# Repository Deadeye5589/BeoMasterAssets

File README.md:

This repo consists of files needed for the BeoMaster Amp project.
It includes
Schematic and layout for main DSP PCB
Schematic and layout for 230 V power distribution PCB
Fusion360 and SVG files to lasercut front display construction
PDS files for left and right display graphics
Square Line Studio projects for left and right display content

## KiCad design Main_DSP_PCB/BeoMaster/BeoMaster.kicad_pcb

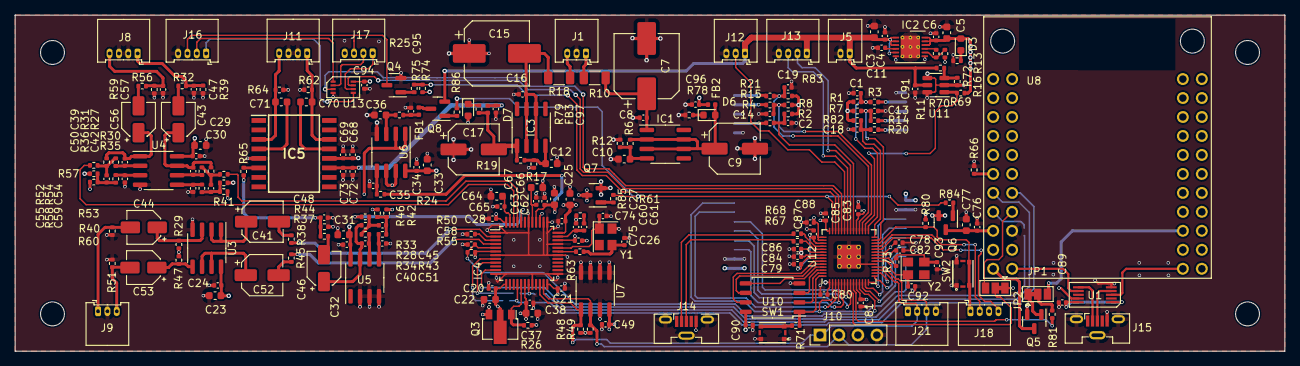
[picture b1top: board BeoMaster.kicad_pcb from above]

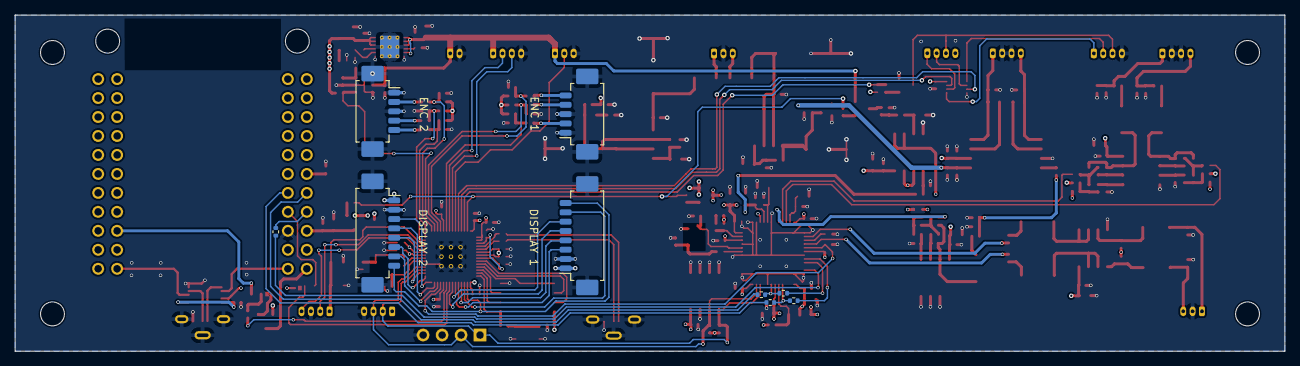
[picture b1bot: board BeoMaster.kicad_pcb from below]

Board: 4 copper layers, 170.0 x 45.0 mm, 238 parts (9 on the bottom side), 160 nets.

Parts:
C1, C2, C4, C6, C13, C14, C18, C19, C20, C21, C24, C26, C27, C28, C30, C32, C34, C35, C38, C49, C58, C63, C65, C67, C69, C73, C76, C89: 100nF; C_0402_1005Metric
C3, C5, C10, C12, C22, C23, C25, C29, C31, C33, C37, C62, C64, C66, C70, C71, C77: 10µF; C_0603_1608Metric
C7, C15: 220µF; CP_Elec_8x10.5
C8, C16: 220nF; C_0402_1005Metric
C9, C17: 100µF; CP_Elec_6.3x5.8
C11, C95, C96, C97: 10nF; C_0402_1005Metric
C36: 2.2µF; C_0603_1608Metric
C39, C40, C50, C51, C54, C59: 150pF; C_0402_1005Metric
C41, C52: 47µF; CP_Elec_5x5.8
C42, C45, C55: 1nF; C_0402_1005Metric
C43, C46, C56: 10µF; CP_Elec_4x5.4
C44, C53: 2.2µF; CP_Elec_4x5.4
C47, C48, C57, C60: 3n3; C_0402_1005Metric
C61: 56nF; C_0402_1005Metric
C68, C72: 1µF; C_0402_1005Metric
C74, C75: 18pF; C_0402_1005Metric
C78, C79, C80, C81, C82, C83, C84, C85, C86, C90, C91, C94: 100n; C_0402_1005Metric
C87, C88: 1u; C_0402_1005Metric
C92, C93: 18p; C_0402_1005Metric
D3, D6, D7: LED; LED_0603_1608Metric
FB1, FB2, FB3: 300@1MHz; L_0402_1005Metric
H1, H2, H3, H4: MountingHole; MountingHole_3.2mm_M3_ISO14580
IC1: LM317L_SO8; SOIC-8_3.9x4.9mm_P1.27mm
IC2: LP38798; WSON-12-1EP_4x4mm_P0.5mm_EP2.6x3mm_ThermalVias
IC3: LM337L_SO8; SOIC-8_3.9x4.9mm_P1.27mm
IC4: ADAU1701JSTZ; LQFP-48_7x7mm_P0.5mm
IC5: DRV134UA; SOIC127P1030X265-16N
J1: 24V_In; Molex_PicoBlade_53048-0310_1x03_P1.25mm_Horizontal
J2: Encoder_Links; Molex_PicoBlade_53261-0571_1x05-1MP_P1.25mm_Horizontal
J3: Encoder_Rechts; Molex_PicoBlade_53261-0571_1x05-1MP_P1.25mm_Horizontal
J4: Display_Links; Molex_PicoBlade_53261-0871_1x08-1MP_P1.25mm_Horizontal
J5: 5V_In; Molex_PicoBlade_53048-0210_1x02_P1.25mm_Horizontal
J6: Display_Rechts; Molex_PicoBlade_53261-0871_1x08-1MP_P1.25mm_Horizontal
J8: Audio_Out; Molex_PicoBlade_53048-0410_1x04_P1.25mm_Horizontal
J9: Aux_In; Molex_PicoBlade_53048-0310_1x03_P1.25mm_Horizontal
J10: DSP_Debugger; PinHeader_1x04_P2.54mm_Vertical
J11: Diff_Out; Molex_PicoBlade_53048-0410_1x04_P1.25mm_Horizontal
J12: WS2812; Molex_PicoBlade_53048-0310_1x03_P1.25mm_Horizontal
J13: 220V_Relais; Molex_PicoBlade_53048-0410_1x04_P1.25mm_Horizontal
J14: RPI_USB; USB_Micro-B_Molex-105133-0031
J15: USB_Audio; USB_Micro-B_Molex-105133-0031
J16: AMP_CTRL1; Molex_PicoBlade_53048-0410_1x04_P1.25mm_Horizontal
J17: AMP_CTRL2; Molex_PicoBlade_53048-0410_1x04_P1.25mm_Horizontal
J18: RP_SWD; Molex_PicoBlade_53048-0410_1x04_P1.25mm_Horizontal
J21: I2C_TempSensor; Molex_PicoBlade_53048-0410_1x04_P1.25mm_Horizontal
JP1, JP2: SolderJumper_3_Bridged12; SolderJumper-3_P1.3mm_Bridged12_Pad1.0x1.5mm
Q3: ZXTP25040DZTA; SOT-89-3
Q4: BC816H; SOT-23
Q5, Q6, Q7, Q8: IRLML2244; SOT-23
R1, R2, R3, R4, R7, R8, R14, R15, R20, R21, R26, R31, R34, R36, R43, R54, R58, R65, R71, R73, R75, R82, R83: 1k; R_0402_1005Metric
R6, R19, R62, R64: 220; R_0402_1005Metric
R10, R18: 100; R_1206_3216Metric
R11: 23k7; R_0402_1005Metric
R12, R17: 2k; R_0402_1005Metric
R13: 180; R_0402_1005Metric
R16: 13k3; R_0402_1005Metric
R24, R30, R33, R35, R42, R53, R55, R57, R66, R69, R70, R74, R80: 10k; R_0402_1005Metric
R25, R29, R47: 100k; R_0402_1005Metric
R27, R28, R41, R46, R52, R60: 22k; R_0402_1005Metric
R32, R37, R56: 680; R_0402_1005Metric
R38, R45, R72: 18k; R_0402_1005Metric
R39, R40, R44, R51, R59: 47k; R_0402_1005Metric
R48, R49: 2k2; R_0402_1005Metric
R50: 18k2; R_0402_1005Metric
R61: 475; R_0402_1005Metric
R63, R81, R84, R85, R86: 100; R_0402_1005Metric
R67, R68: 27; R_0402_1005Metric
R78, R79: 820; R_0402_1005Metric
R87, R88, R89, R90, R91: 22; R_0402_1005Metric
SW1: BOOT; SKSG
SW2: RESET; SKSG
U1: TS3USB30E; TEXAS_VSSOP_10_P0.5
U3, U4, U5, U6: LME49720; SOIC-8_3.9x4.9mm_P1.27mm
U7: 24LC256 (SN); SOIC-8_3.9x4.9mm_P1.27mm
U8: CSRA64215; CSR64215
U10: W25Q128JVS; SOIC-8_5.23x5.23mm_P1.27mm
U11: TPS3711; SOT-23-6
U12: RP2040; RP2040-QFN-56
U13: NC7WZ38; US8 -OnSemi
Y1: 12.288MHz; Crystal_SMD_3225-4Pin_3.2x2.5mm
Y2: 12 MHz; Crystal_SMD_3225-4Pin_3.2x2.5mm

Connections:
+1V1: C78.1, C79.1, C87.1, U12.23 (DVDD), U12.45 (VREG_VOUT), U12.50 (DVDD)
+1V5: R35.1, R42.1, R57.1, U6.6 (-), U6.7
+1V8: C20.1, C21.1, C22.1, IC4.13 (DVDD), IC4.24 (DVDD), Q3.2 (C)
+3.3VP: C25.1, C26.1, C27.1, C28.1, C37.1, C38.1, C49.1, C60.2, IC4.6 (SELFBOOT), IC4.18 (IOVDD), IC4.34 (PVDD), IC4.36 (AVDD), IC4.39 (PLL_MOD1), IC4.48 (AVDD), Q3.3 (E), Q7.3 (D), R26.1, R48.1, R49.1, R55.1, R61.1, U7.8 (VCC)
+3V3: C5.1, C6.1, C80.1, C81.1, C82.1, C83.1, C84.1, C85.1, C86.1, C88.1, C89.1, C90.1, C94.1, D3.2 (A), IC2.10 (OUT_(FB)), IC2.11 (OUT), IC2.12 (OUT), J4.1, J6.1, J21.1, Q5.2 (S), Q6.2 (S), Q7.2 (S), R1.2, R2.2, R7.2, R8.2, R69.1, R74.1, R80.1, R82.2, R83.2, U1.1 (S), U1.10 (Vcc), U10.8 (VCC), U12.1 (IOVDD), U12.10 (IOVDD), U12.22 (IOVDD), U12.33 (IOVDD), U12.42 (IOVDD), U12.43 (ADC_AVDD), U12.44 (VREG_IN), U12.48 (USB_VDD), U12.49 (IOVDD), U13.8 (Vcc)
+5V: C3.1, C4.1, C91.1, IC2.1 (IN), IC2.2 (IN), IC2.3 (IN_(CP)), IC2.5 (EN), J5.1, J12.1, J13.1, Q8.2 (S), R70.1, U11.5 (VDD)
+5VA: R29.1, R41.2, R46.2, R47.1, R60.2, U6.1, U6.2 (-)
+12V: C23.1, C24.1, C29.1, C30.1, C31.1, C32.1, C33.1, C34.1, C68.1, C69.1, C96.1, FB2.2, IC5.12 (V+), U3.8 (V+), U4.8 (V+), U5.8 (V+), U6.8 (V+)
-12V: C72.2, C73.2, C97.2, FB3.2, IC5.11 (V-)
/AMP_MUTE: R74.2, R75.2, U12.40 (GPIO28_ADC2)
/QSPI_SCLK: U10.6 (CLK), U12.52 (QSPI_SCLK)
/QSPI_SD0: U10.5 (DI(IO0)), U12.53 (QSPI_SD0)
/QSPI_SD1: U10.2 (DO(IO1)), U12.55 (QSPI_SD1)
/QSPI_SD2: U10.3 (IO2), U12.54 (QSPI_SD2)
/QSPI_SD3: U10.7 (IO3), U12.51 (QSPI_SD3)
/QSPI_SS: R71.1, U10.1 (~CS), U12.56 (QSPI_SS)
/RUN: J18.1, R80.2, SW2.2, U12.26 (RUN)
/SSR1: J13.2, U12.35 (GPIO23)
/SSR2: J13.3, U12.36 (GPIO24)
/SWCLK: J18.4, U12.24 (SWCLK)
/SWD: J18.2, U12.25 (SWD)
/USB_D+: J14.3 (D+), R67.1
/USB_D-: J14.2 (D-), R68.1
/USB_N: U1.7 (D2-), U8.2 (USBN)
/USB_P: U1.3 (D2+), U8.23 (USBP)
/V_SENS: R69.2, U11.1 (OUT), U12.30 (GPIO19)
/Vin+: J1.1, R10.1
/Vin-: J1.3, R18.1
/XIN: C92.1, U12.20 (XIN), Y2.1
/XOUT: R73.1, U12.21 (XOUT)
/~USB_BOOT: R71.2, SW1.2
AMP_MUTE_CONN: J16.3, J17.3, Q4.3 (C)
AMP_OC: U12.39 (GPIO27_ADC1), U13.7 (Y1)
AMP_TEMP: U12.38 (GPIO26_ADC0), U13.3 (Y2)
Analog_In0: IC4.45 (VOUT1), R30.1
Analog_In1: IC4.46 (VOUT0), R53.1
Analog_Out0: C47.1, J8.1, R32.2, R39.1
Analog_Out1: C57.1, J8.4, R56.2, R59.1
BCLK: R90.2, U8.9 (CLK)
BT_MFB: R81.1, U12.9 (GPIO7)
BT_RST: JP2.2 (C), U12.8 (GPIO6)
CM: C62.1, C63.1, IC4.40 (CM), R24.2
DISP_BL: J4.8, J6.8, U12.2 (GPIO0)
DISP_CLK1: J4.4, U12.13 (GPIO10)
DISP_CLK2: J6.4, U12.4 (GPIO2)
DISP_CS1: J4.5, U12.16 (GPIO13)
DISP_CS2: J6.5, U12.7 (GPIO5)
DISP_DC1: J4.6, U12.15 (GPIO12)
DISP_DC2: J6.6, U12.6 (GPIO4)
DISP_DIN1: J4.3, U12.14 (GPIO11)
DISP_DIN2: J6.3, U12.5 (GPIO3)
DISP_RST1: J4.7, U12.12 (GPIO9)
DISP_RST2: J6.7, U12.3 (GPIO1)
DSP_RESET: C58.1, IC4.5 (~RESET), J10.3, R55.2, U12.11 (GPIO8)
Diff_In0: IC4.44 (VOUT2), R33.1
Diff_Out0: C48.1, R37.2, R44.1, R65.2
Diff_Out0+: C70.1, IC5.14 (+Vo), J11.1, R62.1
Diff_Out0-: C71.2, IC5.3 (-Vo), J11.4, R64.2
ENC1_A: C13.1, R7.1, R14.2, U12.27 (GPIO16)
ENC1_B: C18.1, R20.2, R82.1, U12.28 (GPIO17)
ENC1_SW: C1.1, R1.1, R3.2, U12.29 (GPIO18)
ENC2_A: C14.1, R8.1, R15.2, U12.31 (GPIO20)
ENC2_B: C19.1, R21.2, R83.1, U12.32 (GPIO21)
ENC2_SW: C2.1, R2.1, R4.2, U12.34 (GPIO22)
GND: C1.2, C2.2, C3.2, C4.2, C5.2, C6.2, C7.2, C8.2, C9.2, C10.2, C11.2, C12.2, C13.2, C14.2, C15.1, C16.2, C17.1, C18.2, C19.2, C20.2, C21.2, C22.2, C23.2, C24.2, C25.2, C26.2, C27.2, C28.2, C29.2, C30.2, C31.2, C32.2, C33.2, C34.2, C35.2, C36.2, C37.2, C38.2, C47.2, C48.2, C49.2, C50.2, C51.2, C57.2, C58.2, C59.2, C62.2, C63.2, C64.2, C65.2, C66.2, C67.2, C68.2, C69.2, C72.1, C73.1, C74.2, C75.2, C76.2, C77.2, C78.2, C79.2, C80.2, C81.2, C82.2, C83.2, C84.2, C85.2, C86.2, C87.2, C88.2, C89.2, C90.2, C91.2, C92.2, C93.2, C94.2, C95.2, C96.2, C97.1, D7.2 (A), IC2.6 (GND_(CP)), IC2.7 (GND), IC2.13 (EP), IC4.1 (AGND), IC4.7 (ADDR0), IC4.12 (DGND), IC4.20 (ADDR1), IC4.25 (DGND), IC4.30 (RSVD), IC4.33 (PGND), IC4.37 (AGND), IC4.38 (PLL_MOD0), IC4.42 (AGND), IC5.5 (GND), J1.2, J2.1, J2.3, J2.MP, J3.1, J3.3, J3.MP, J4.2, J4.MP, J5.2, J6.2, J6.MP, J8.2, J8.3, J9.2, J10.4, J11.2, J11.3, J12.3, J13.4, J14.5 (GND), J14.6 (Shield), J15.5 (GND), J15.6 (Shield), J16.4, J18.3, J21.4, Q4.2 (E), R12.2, R13.2, R16.2, R17.1, R39.2, R40.2, R44.2, R50.2, R51.2, R59.2, R62.2, R64.1, R66.2, R72.2, R78.2, SW1.1, SW2.1, U1.5 (GND), U3.4 (V-), U4.4 (V-), U5.2 (-), U5.3 (+), U5.4 (V-), U6.4 (V-), U7.1 (A0), U7.2 (A1), U7.3 (A2), U7.4 (GND), U7.7 (WP), U8.6 (GND), U10.4 (GND), U11.2 (GND), U11.4 (GND), U11.6 (GND), U12.19 (TESTEN), U12.57 (GND), U13.4 (GND), Y1.4
LRCLK: R91.2, U8.10 (CSB)
unnamed: C15.2, C16.1, IC3.2 (VI), IC3.3 (VI), IC3.6 (VI), IC3.7 (VI), R18.2
unnamed: C39.1, C43.1, R27.1, U4.7
unnamed: C40.1, C46.1, R28.1, U5.7
unnamed: C41.2, R38.2
unnamed: C42.1, R27.2, R30.2, R31.1
unnamed: C42.2, R35.2, R36.2, R41.1
unnamed: C43.2, R32.1
unnamed: C45.1, R28.2, R33.2, R34.1
unnamed: C45.2, R42.2, R43.2, R46.1
unnamed: C46.2, R37.1
unnamed: C52.2, R45.2
unnamed: C54.1, C56.1, R52.1, U4.1
unnamed: C55.1, R52.2, R53.2, R54.1
unnamed: C55.2, R57.2, R58.2, R60.1
unnamed: C56.2, R56.1
unnamed: C61.2, R61.2
unnamed: C75.1, R63.2, Y1.3
unnamed: C93.1, R73.2, Y2.3
unnamed: C95.1, FB1.2, R25.2
unnamed: D3.1 (K), R13.1
unnamed: C9.1, D6.2 (A), FB2.1, IC1.2 (VO), IC1.3 (VO), IC1.6 (VO), IC1.7 (VO), R6.1
unnamed: D6.1 (K), R78.1
unnamed: D7.1 (K), R79.1
unnamed: C10.1, IC1.4 (ADJ), R6.2, R12.1
unnamed: C7.1, C8.1, IC1.1 (VI), R10.2
unnamed: C11.1, IC2.4 (CP)
unnamed: IC2.8 (FB), R11.2, R16.1
unnamed: IC2.9 (SET), R11.1
unnamed: C12.1, IC3.4 (ADJ), R17.2, R19.1
unnamed: C17.2, FB3.1, IC3.1 (VO), R19.2, R79.2
unnamed: IC4.2 (ADC0), R38.1
unnamed: IC4.4 (ADC1), R45.1
unnamed: IC4.3 (ADC_RES), R50.1
unnamed: C64.1, C65.1, IC4.47 (FILTA)
unnamed: C66.1, C67.1, IC4.41 (FILTD)
unnamed: C74.1, IC4.32 (MCLKI), Y1.1
unnamed: IC4.8 (MP4), R89.1
unnamed: IC4.9 (MP5), R88.1
unnamed: IC4.16 (MP10), R89.2, R91.1
unnamed: IC4.19 (MP11), R88.2, R90.1
unnamed: IC4.31 (OSCO), R63.1
unnamed: C60.1, C61.1, IC4.35 (PLL_LF)
unnamed: IC4.17 (VDRIVE), Q3.1 (B), R26.2
unnamed: C70.2, IC5.13 (+Sense)
unnamed: C71.1, IC5.4 (-Sense)
unnamed: IC5.6 (Vin), R65.1
unnamed: J2.2, R3.1
unnamed: J2.4, R14.1
unnamed: J2.5, R20.1
unnamed: J3.2, R4.1
unnamed: J3.4, R15.1
unnamed: J3.5, R21.1
unnamed: C44.2, J9.1, R40.1
unnamed: C53.2, J9.3, R51.1
unnamed: J15.3 (D+), U1.4 (D+)
unnamed: J15.2 (D-), U1.6 (D-)
unnamed: J16.1, U13.5 (A2)
unnamed: J16.2, U13.1 (A1)
unnamed: J17.1, U13.6 (B2)
unnamed: J17.2, U13.2 (B1)
unnamed: JP1.1 (A), Q5.1 (G)
unnamed: JP1.3 (B), U8.27 (MFB)
unnamed: JP1.2 (C), R81.2
unnamed: JP2.1 (A), U1.9 (~OE)
unnamed: JP2.3 (B), U8.8 (RST)
unnamed: Q4.1 (B), R75.1
unnamed: Q5.3 (D), U8.1 (VCHG)
unnamed: C76.1, C77.1, Q6.3 (D), U8.5 (VBAT)
unnamed: Q6.1 (G), R84.2
unnamed: Q7.1 (G), R85.2
unnamed: FB1.1, Q8.3 (D)
unnamed: Q8.1 (G), R86.2
unnamed: C44.1, R29.2, U3.3 (+)
unnamed: C41.1, U3.1, U3.2 (-)
unnamed: C53.1, R47.2, U3.5 (+)
unnamed: C52.1, U3.6 (-), U3.7
unnamed: C59.1, R58.1, U4.3 (+)
unnamed: C54.2, R54.2, U4.2 (-)
unnamed: C50.1, R36.1, U4.5 (+)
unnamed: C39.2, R31.2, U4.6 (-)
unnamed: C51.1, R43.1, U5.5 (+)
unnamed: C40.2, R34.2, U5.6 (-)
unnamed: C36.1, R25.1, U6.3 (+)
unnamed: C35.1, R24.1, U6.5 (+)
unnamed: R87.1, U8.7 (MISO)
unnamed: R66.1, U8.11 (SPIPCM)
unnamed: R70.2, R72.1, U11.3 (SENSE)
unnamed: R68.2, U12.46 (USB_DM)
unnamed: R67.2, U12.47 (USB_DP)
PWR_EN: R84.1, R85.1, R86.1, U12.41 (GPIO29_ADC3)
SCL: IC4.23 (SCL), J10.2, J21.3, R49.2, U7.6 (SCL), U12.18 (GPIO15)
SDA: IC4.22 (SDA), J10.1, J21.2, R48.2, U7.5 (SDA), U12.17 (GPIO14)
SDATA: IC4.11 (MP0), R87.2
WS2812: J12.2, U12.37 (GPIO25)

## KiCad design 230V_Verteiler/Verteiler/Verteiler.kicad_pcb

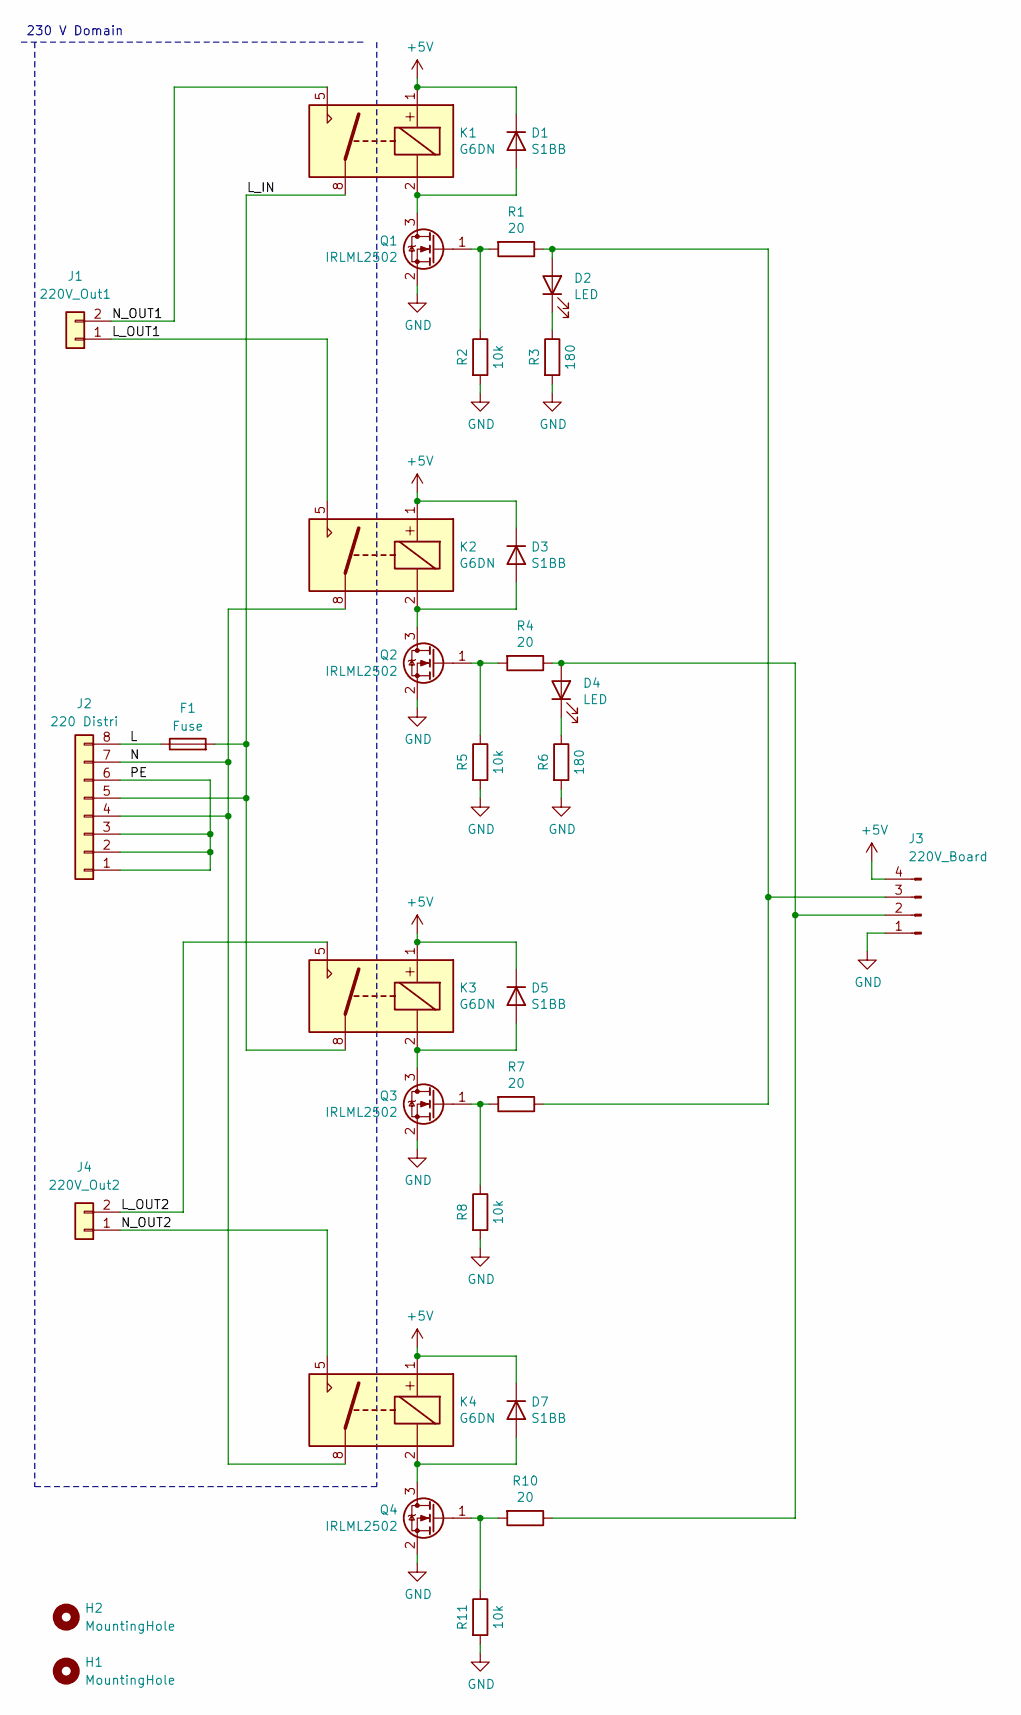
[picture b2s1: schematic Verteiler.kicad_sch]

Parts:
D1, D3, D5, D7: S1BB; D_SMB
D2, D4: LED; LED_0603_1608Metric
F1: Fuse; Fuseholder_Clip-5x20mm_Littelfuse_111_Lateral_P18.80x5.00mm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
H1, H2: MountingHole; MountingHole_3.2mm_M3
J1: 220V_Out1; PhoenixContact_MSTBA_2,5_2-G-5,08_1x02_P5.08mm_Horizontal
J2: 220 Distri; PhoenixContact_MSTBA_2,5_8-G-5,08_1x08_P5.08mm_Horizontal
J3: 220V_Board; Molex_PicoBlade_53048-0410_1x04_P1.25mm_Horizontal
J4: 220V_Out2; PhoenixContact_MSTBA_2,5_2-G-5,08_1x02_P5.08mm_Horizontal
K1, K2, K3, K4: G6DN
Q1, Q2, Q3, Q4: IRLML2502; SOT-23
R1, R4, R7, R10: 20; R_0402_1005Metric
R2, R5, R8, R11: 10k; R_0402_1005Metric
R3, R6: 180; R_0402_1005Metric

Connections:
+5V: D1.1 (K), D3.1 (K), D5.1 (K), D7.1 (K), J3.4, K1.1, K2.1, K3.1, K4.1
/L: F1.1, J2.8
/L_IN: F1.2, J2.5, K1.8, K3.8
/L_OUT1: J1.1, K2.5
/L_OUT2: J4.2, K3.5
/N: J2.4, J2.7, K2.8, K4.8
/N_OUT1: J1.2, K1.5
/N_OUT2: J4.1, K4.5
/PE: J2.1, J2.2, J2.3, J2.6
GND: J3.1, Q1.2 (S), Q2.2 (S), Q3.2 (S), Q4.2 (S), R2.2, R3.2, R5.2, R6.2, R8.2, R11.2
unnamed: D1.2 (A), K1.2, Q1.3 (D)
unnamed: D2.2 (A), J3.3, R1.1, R7.1
unnamed: D2.1 (K), R3.1
unnamed: D3.2 (A), K2.2, Q2.3 (D)
unnamed: D4.2 (A), J3.2, R4.1, R10.1
unnamed: D4.1 (K), R6.1
unnamed: D5.2 (A), K3.2, Q3.3 (D)
unnamed: D7.2 (A), K4.2, Q4.3 (D)
unnamed: Q1.1 (G), R1.2, R2.1
unnamed: Q2.1 (G), R4.2, R5.1
unnamed: Q3.1 (G), R7.2, R8.1
unnamed: Q4.1 (G), R10.2, R11.1

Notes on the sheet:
230 V Domain

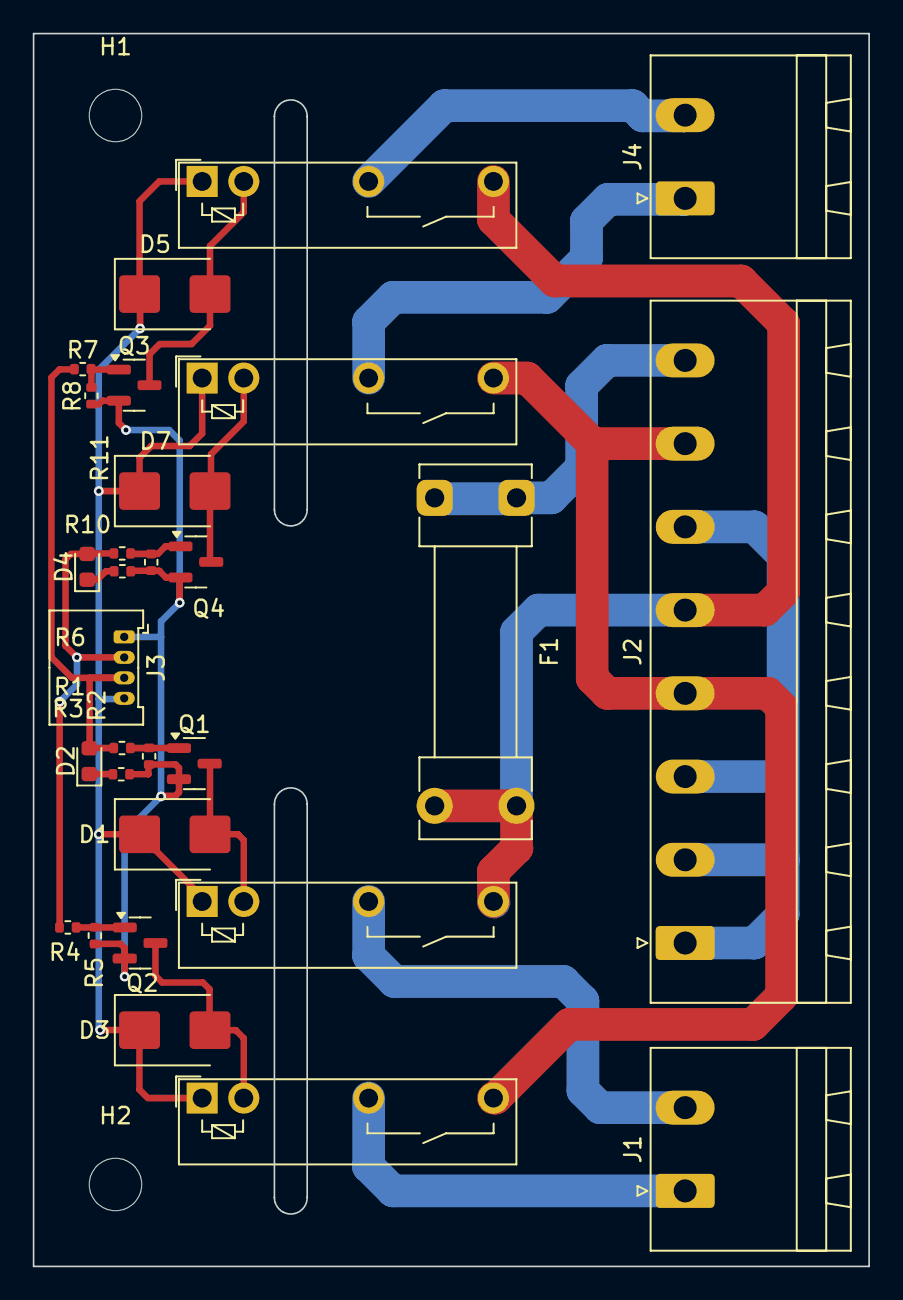
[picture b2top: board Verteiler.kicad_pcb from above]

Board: 2 copper layers, 51.0 x 75.2 mm, 31 parts (0 on the bottom side), 22 nets.

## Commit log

2023-05-11 Display Graphics
2025-12-31 New Layout with Setup Page
    Changed Page 2 - Instead of 20 Band now 2 x 7 Band EQ Bars
    Changed Page 3 - Configuration Page for DSP parameters
2026-01-02 Assets for Sqaure Line Studio
    Date needed for generation of the display layouts and source code via SquareLine Studio
2026-01-02 SquareLine Project files
2026-01-12 Font Color
    Changed font color in setup menu to white for better readability.
2026-01-30 Extended character Range
    Not included letters a-Z, A-Z and °
2026-01-30 Dateien für die Fontblende
    Passend zu Gehäuse W215 H62 D308 (BZ2206HT)
    https://de.aliexpress.com/item/4001301808056.html?spm=a2g0o.order_list.order_list_main.187.21f21802w0dpip&gatewayAdapt=glo2deu
    2x Waveshare 1.9 Inch LCD 170x320 px
    https://www.waveshare.com/1.9inch-lcd-module.htm
2026-01-30 DSP Configuration
    Complete DSP configuration for the BeoMaster Amp
    Works with SigmaStudio 4.7
2026-01-30 Create SquareLineStudio
2026-01-30 Relais Board for BeoMaster Amp
    KiCad 9 Files for 230 V distribution PCB of BeoMaster Amp
2026-01-30 Main DSP PCB for BeoMaster Amp
    Revision 3 of the DSP PCB, now standing upright behind the displays to save space inside the housing.
    Works in combination with 230 V Distribution PCB.
2026-01-30 Design Files for display graphics
    Graphics designed in photoshop
    Then used in SquareLineStudio V1.3 with LVGL 8.3.10 (breaking changes with newer versions of LVGL)
    Assets generated within SLS
2026-01-30 Fusion 360 files of front display construction
2026-01-30 Fusion 360 for BeoMaster Amp
    Carrier Plate for IcePower ASX Amps, Meanwell 5V power supply, main DSP PCB and 230 V distribution PCB
